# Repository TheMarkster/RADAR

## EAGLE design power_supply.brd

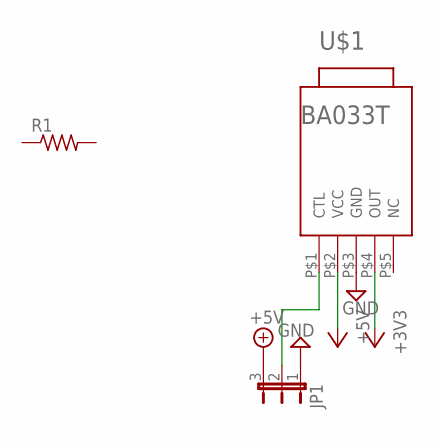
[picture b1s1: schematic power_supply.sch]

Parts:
JP1: JP2E; JP2
R1: R-US_R0603; R0603
U$1: BA033T; TO220FP-5

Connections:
+3V3: U$1.P$4 (OUT)
+5V: JP1.3, U$1.P$2 (VCC)
GND: JP1.1, U$1.P$3 (GND)
unnamed: JP1.2, U$1.P$1 (CTL)

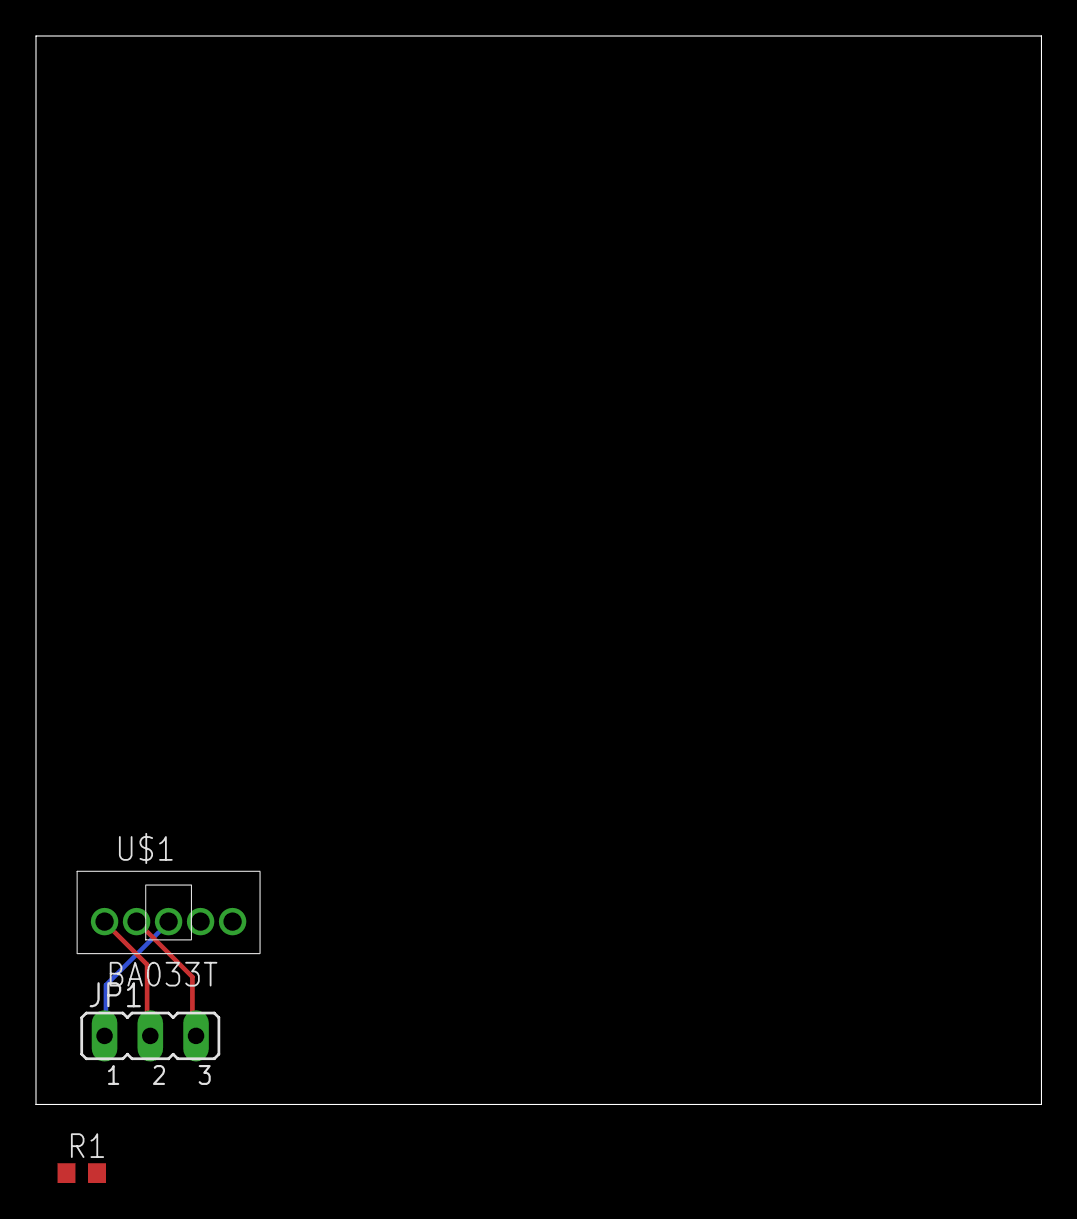
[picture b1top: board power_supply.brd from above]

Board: 2 copper layers, 55.9 x 59.4 mm, 3 parts (0 on the bottom side), 3 nets.

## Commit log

2015-05-27 :tada: Added .gitattributes & .gitignore files
2015-05-27 Initial Board Files
